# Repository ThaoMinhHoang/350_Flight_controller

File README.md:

# ECTE350 Flight controller
ECTE350 storage room for Locus team

Save the kicad files of your sensor. Put them into a folder. Name the folder after your sensor. Upload the folder to github.

The Development folder is all of our work in the one kicad file. Don't fuck with it unless you know what you're doing :)

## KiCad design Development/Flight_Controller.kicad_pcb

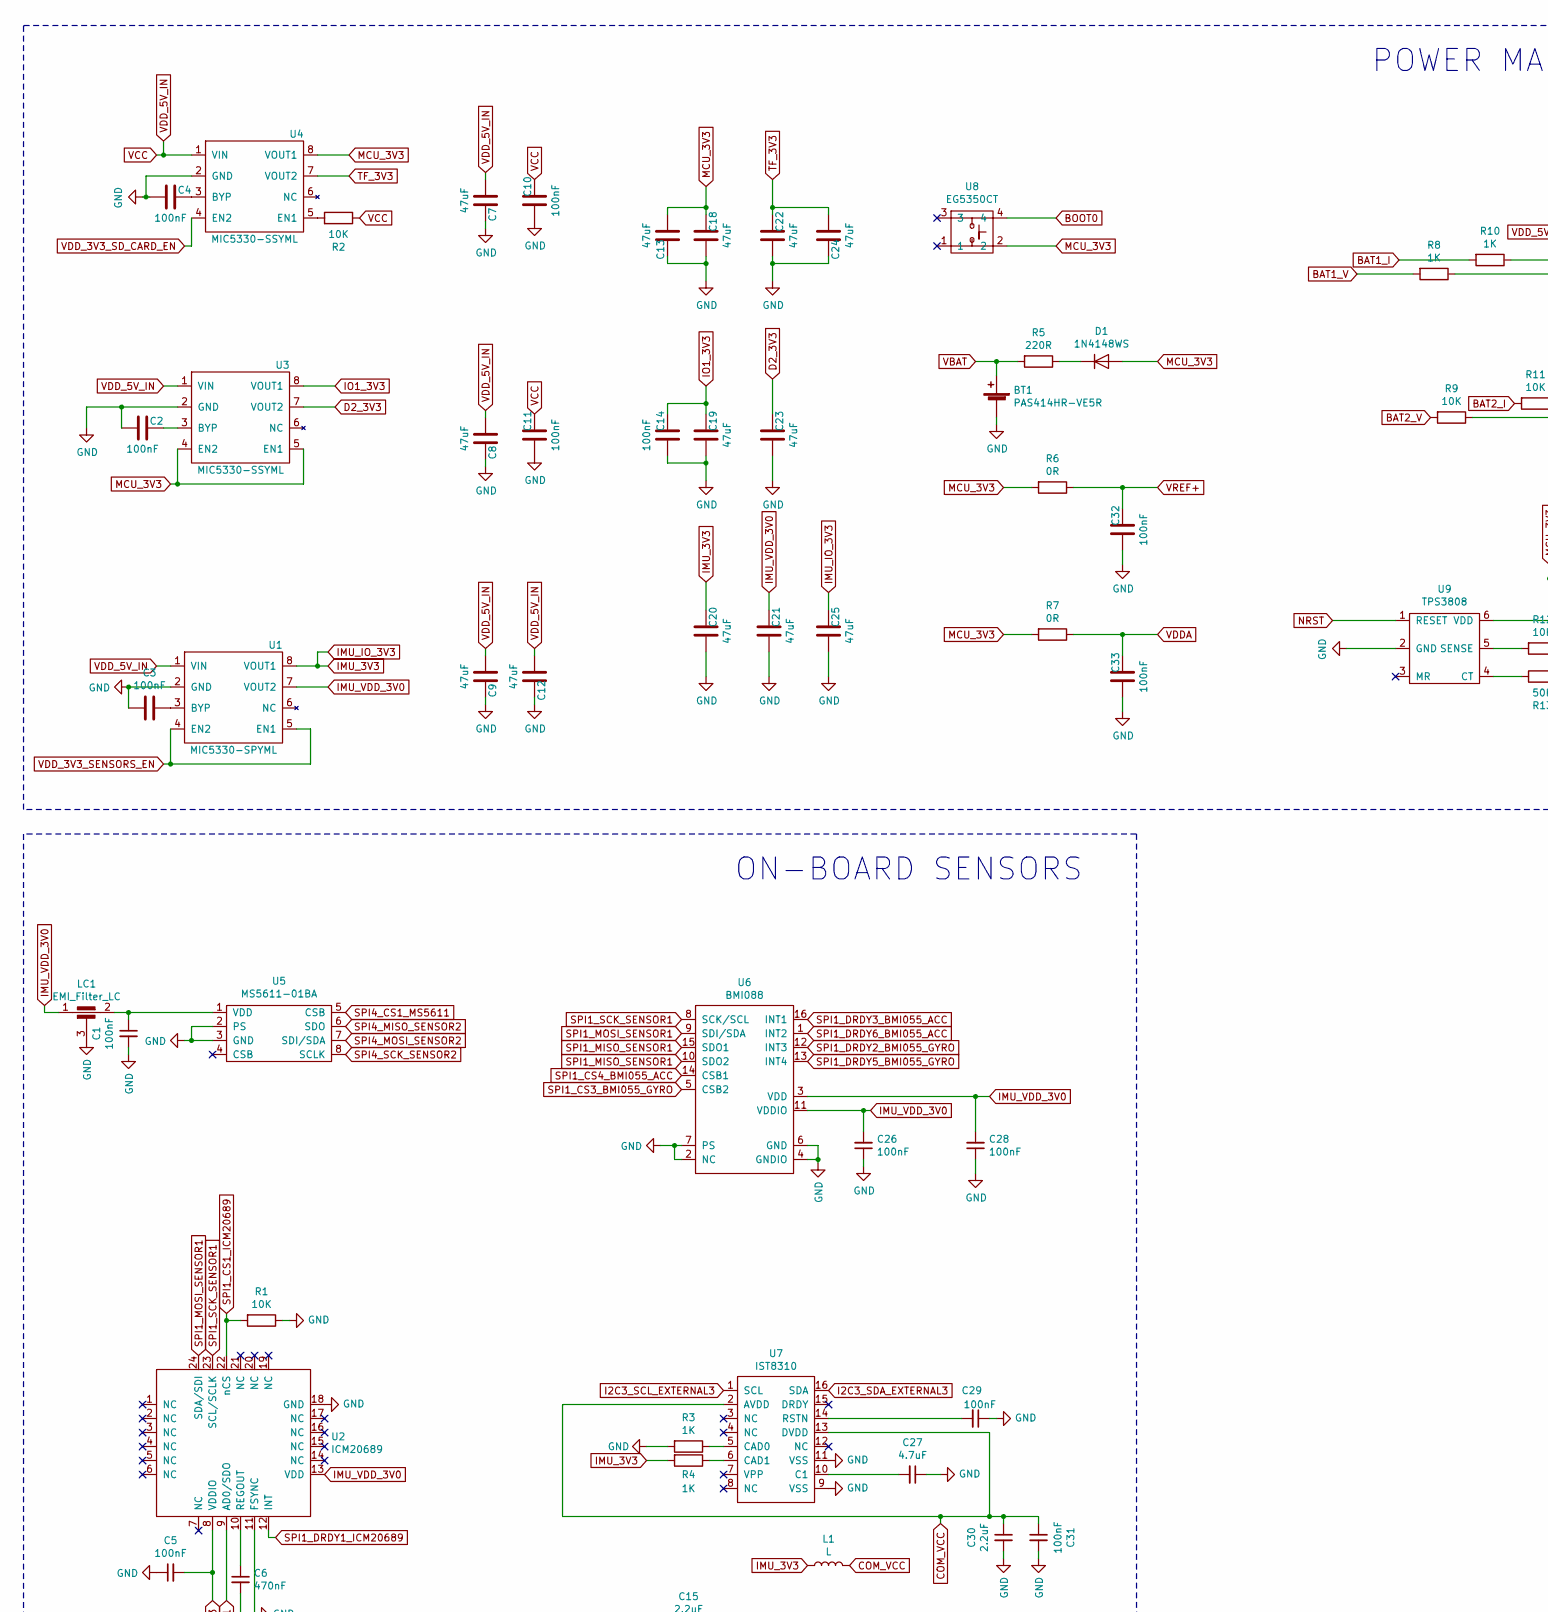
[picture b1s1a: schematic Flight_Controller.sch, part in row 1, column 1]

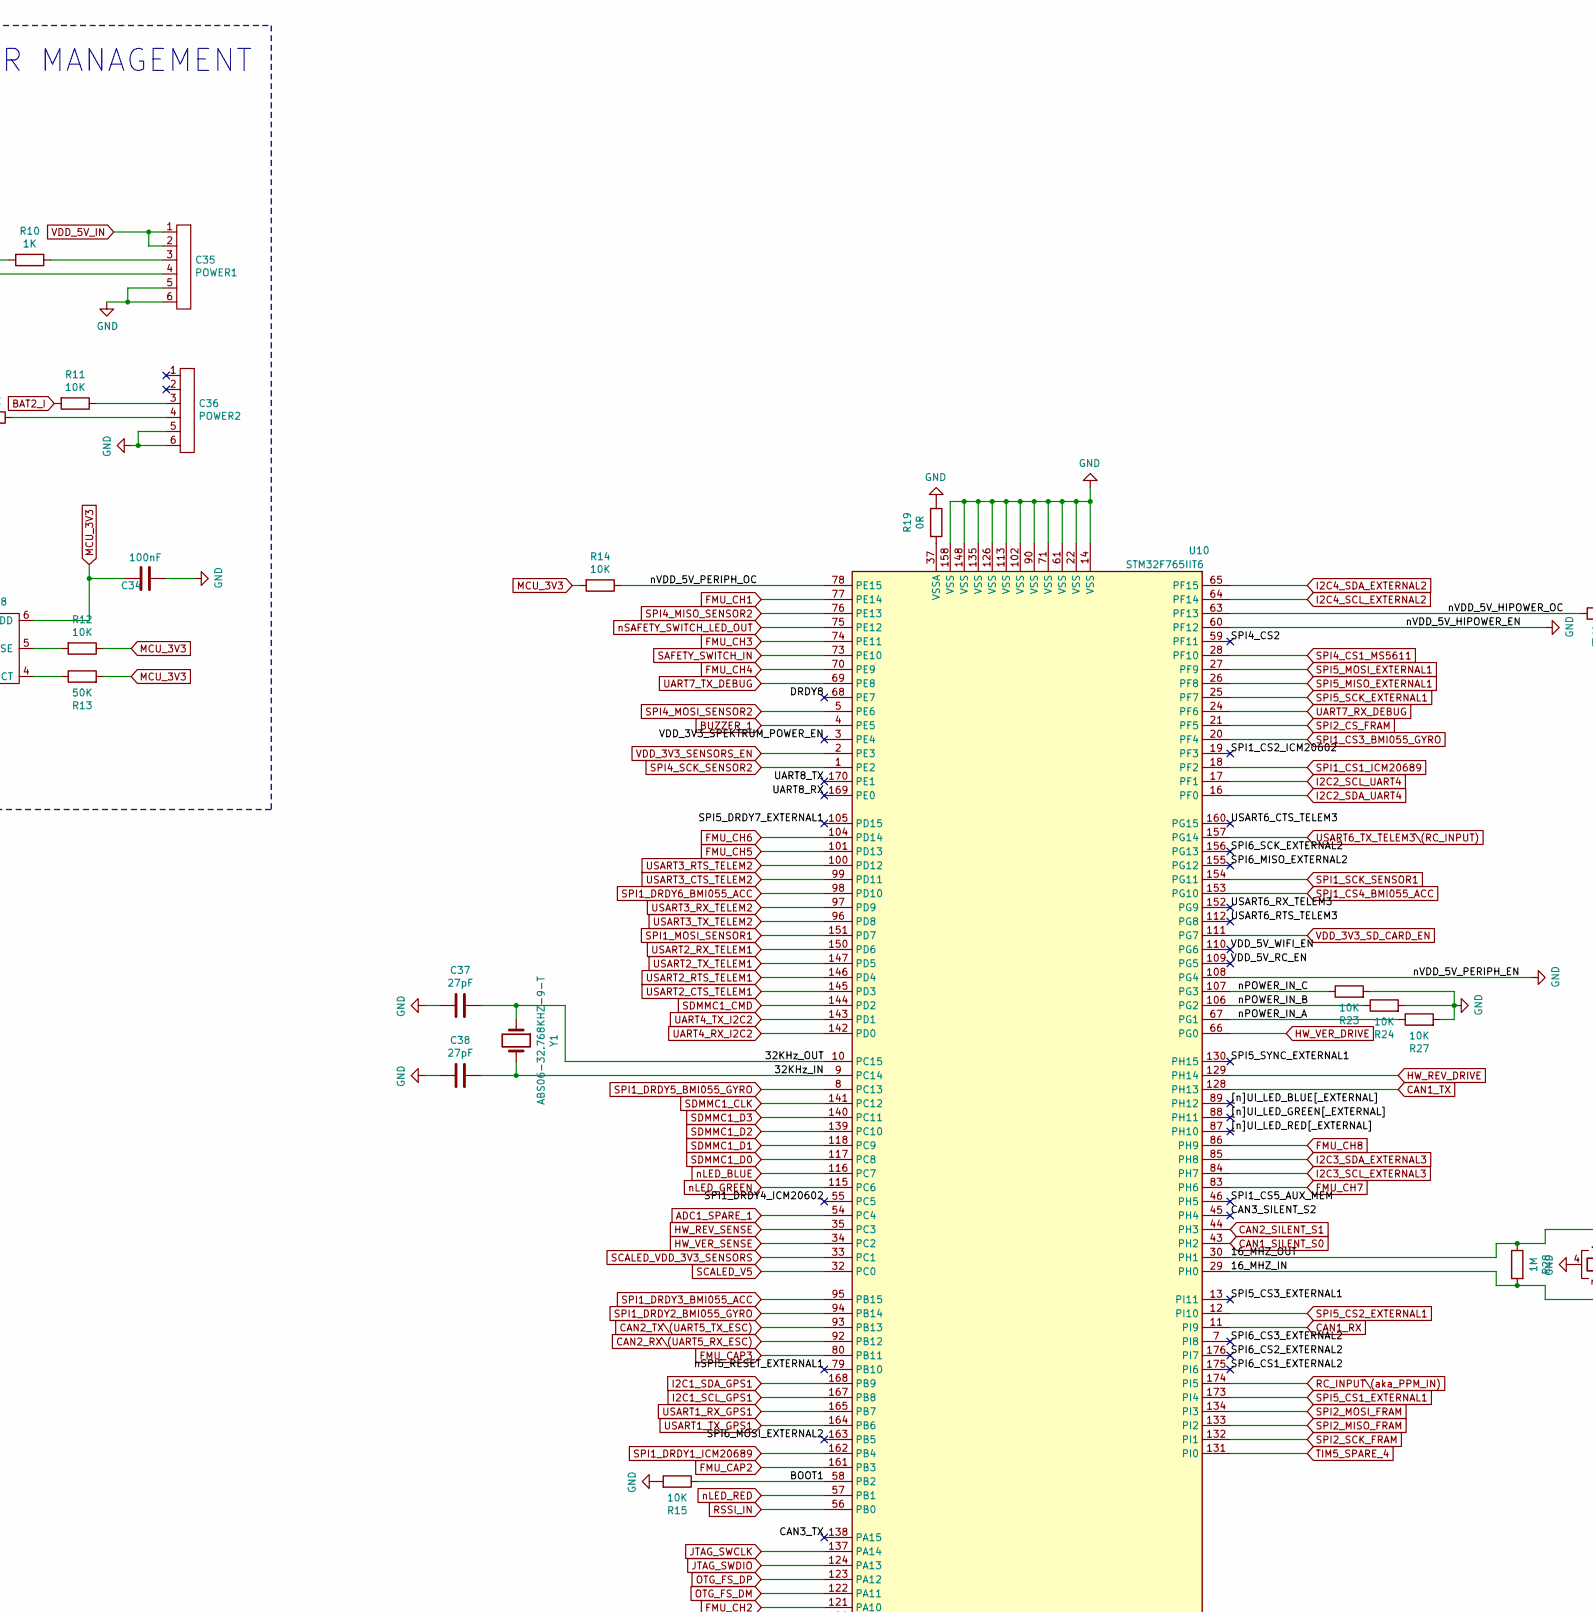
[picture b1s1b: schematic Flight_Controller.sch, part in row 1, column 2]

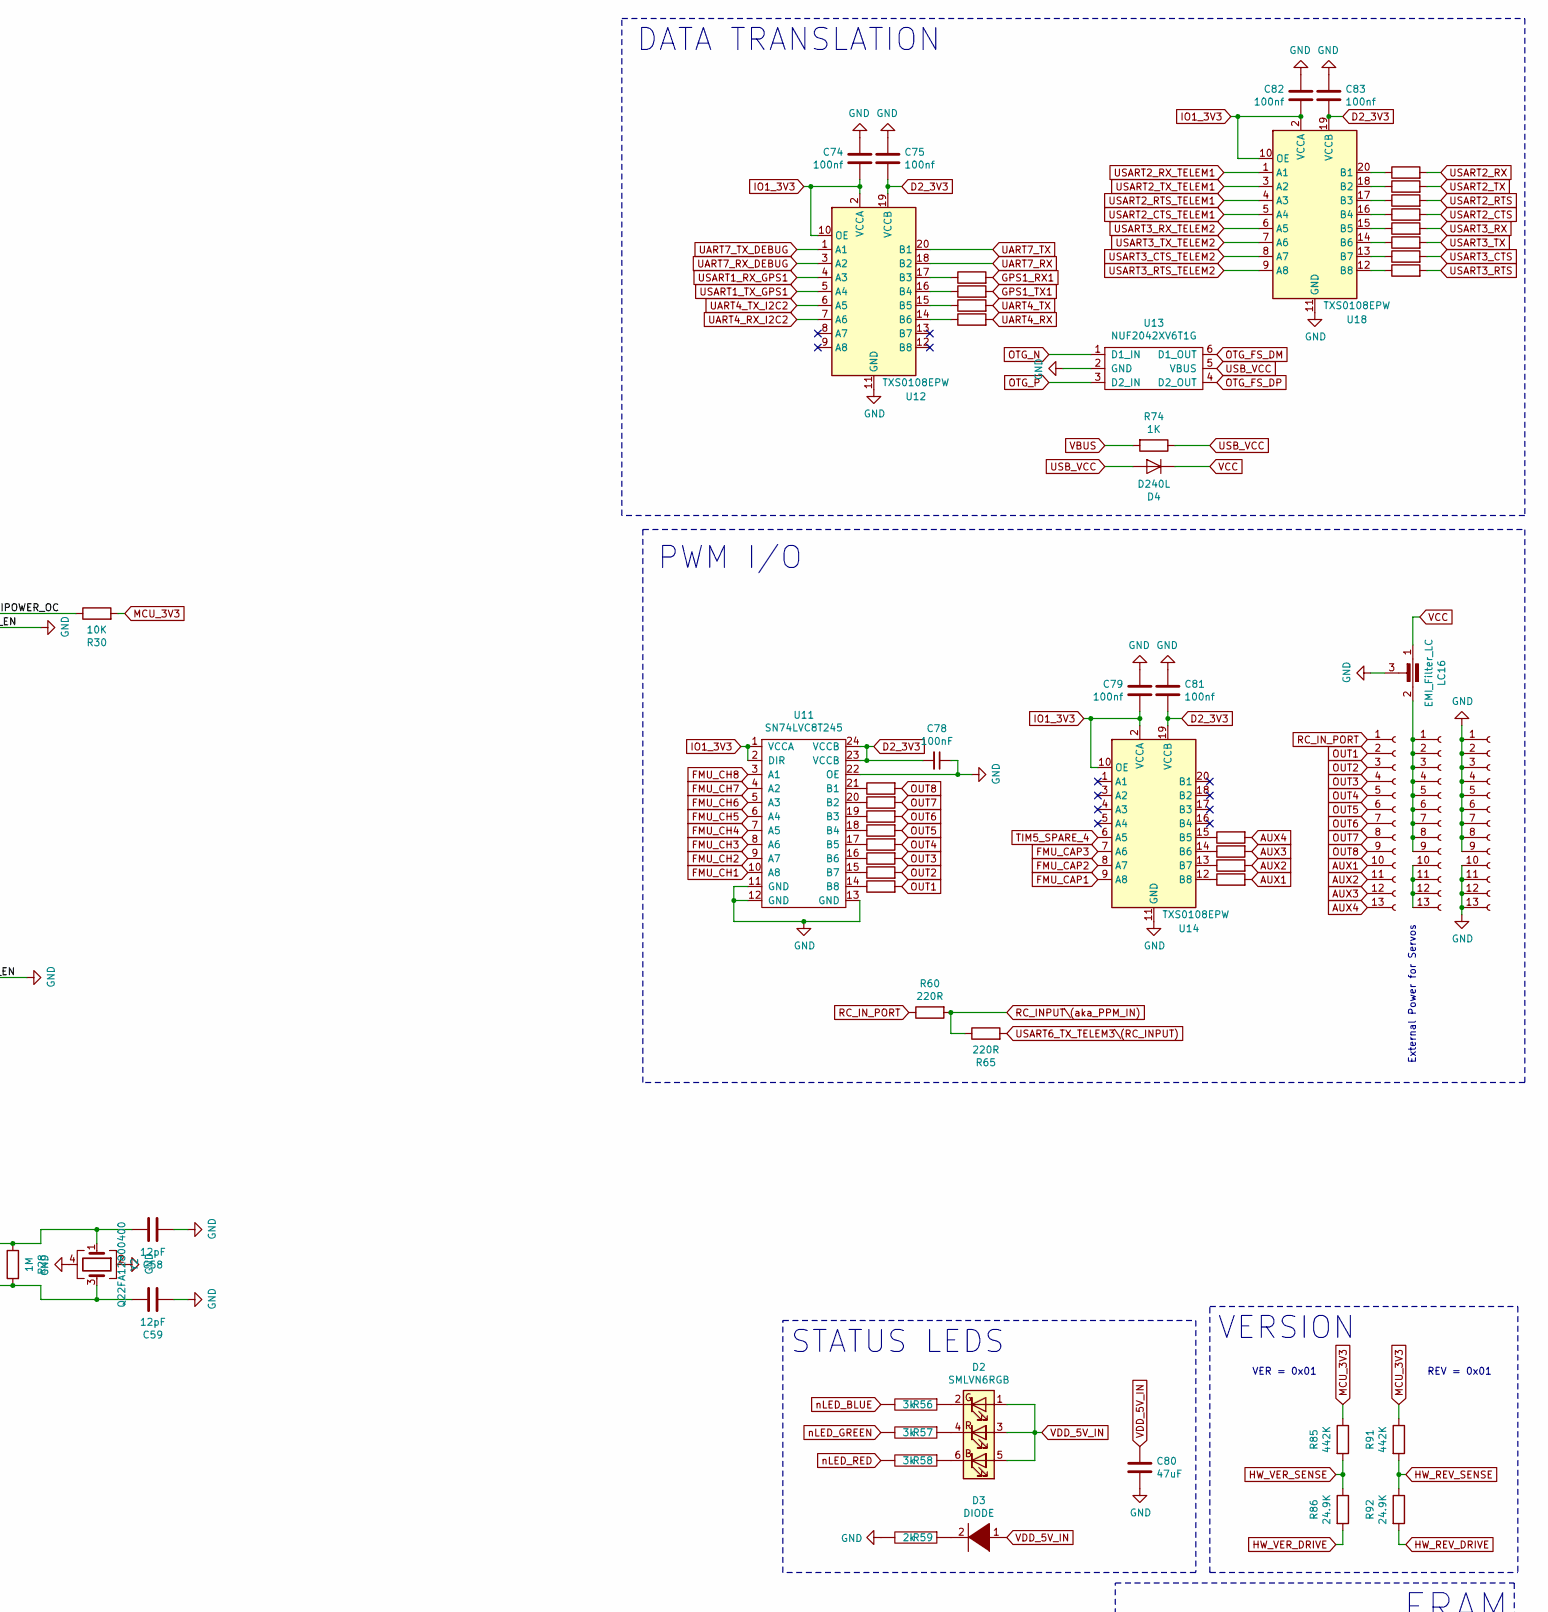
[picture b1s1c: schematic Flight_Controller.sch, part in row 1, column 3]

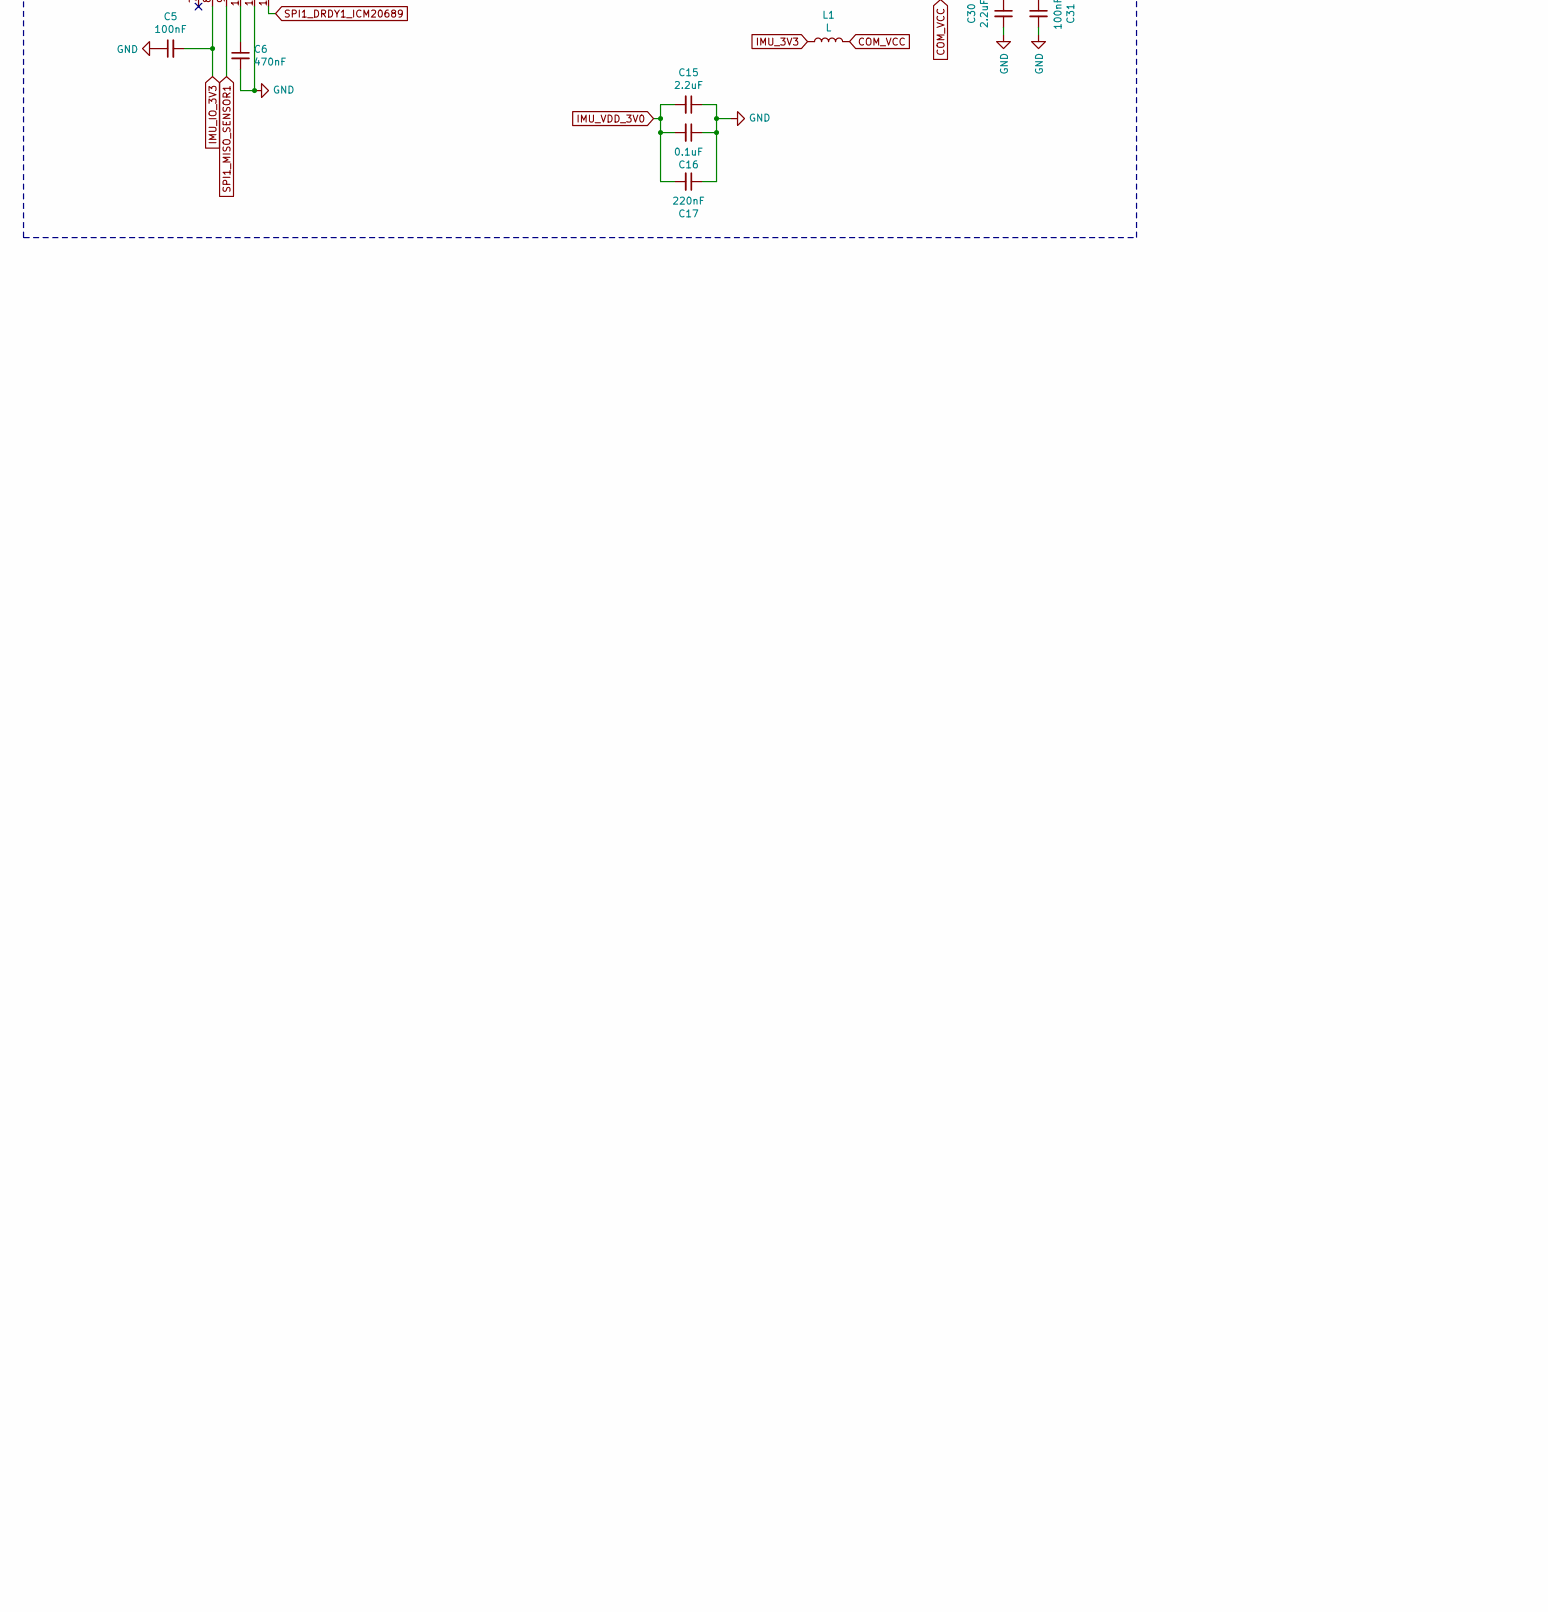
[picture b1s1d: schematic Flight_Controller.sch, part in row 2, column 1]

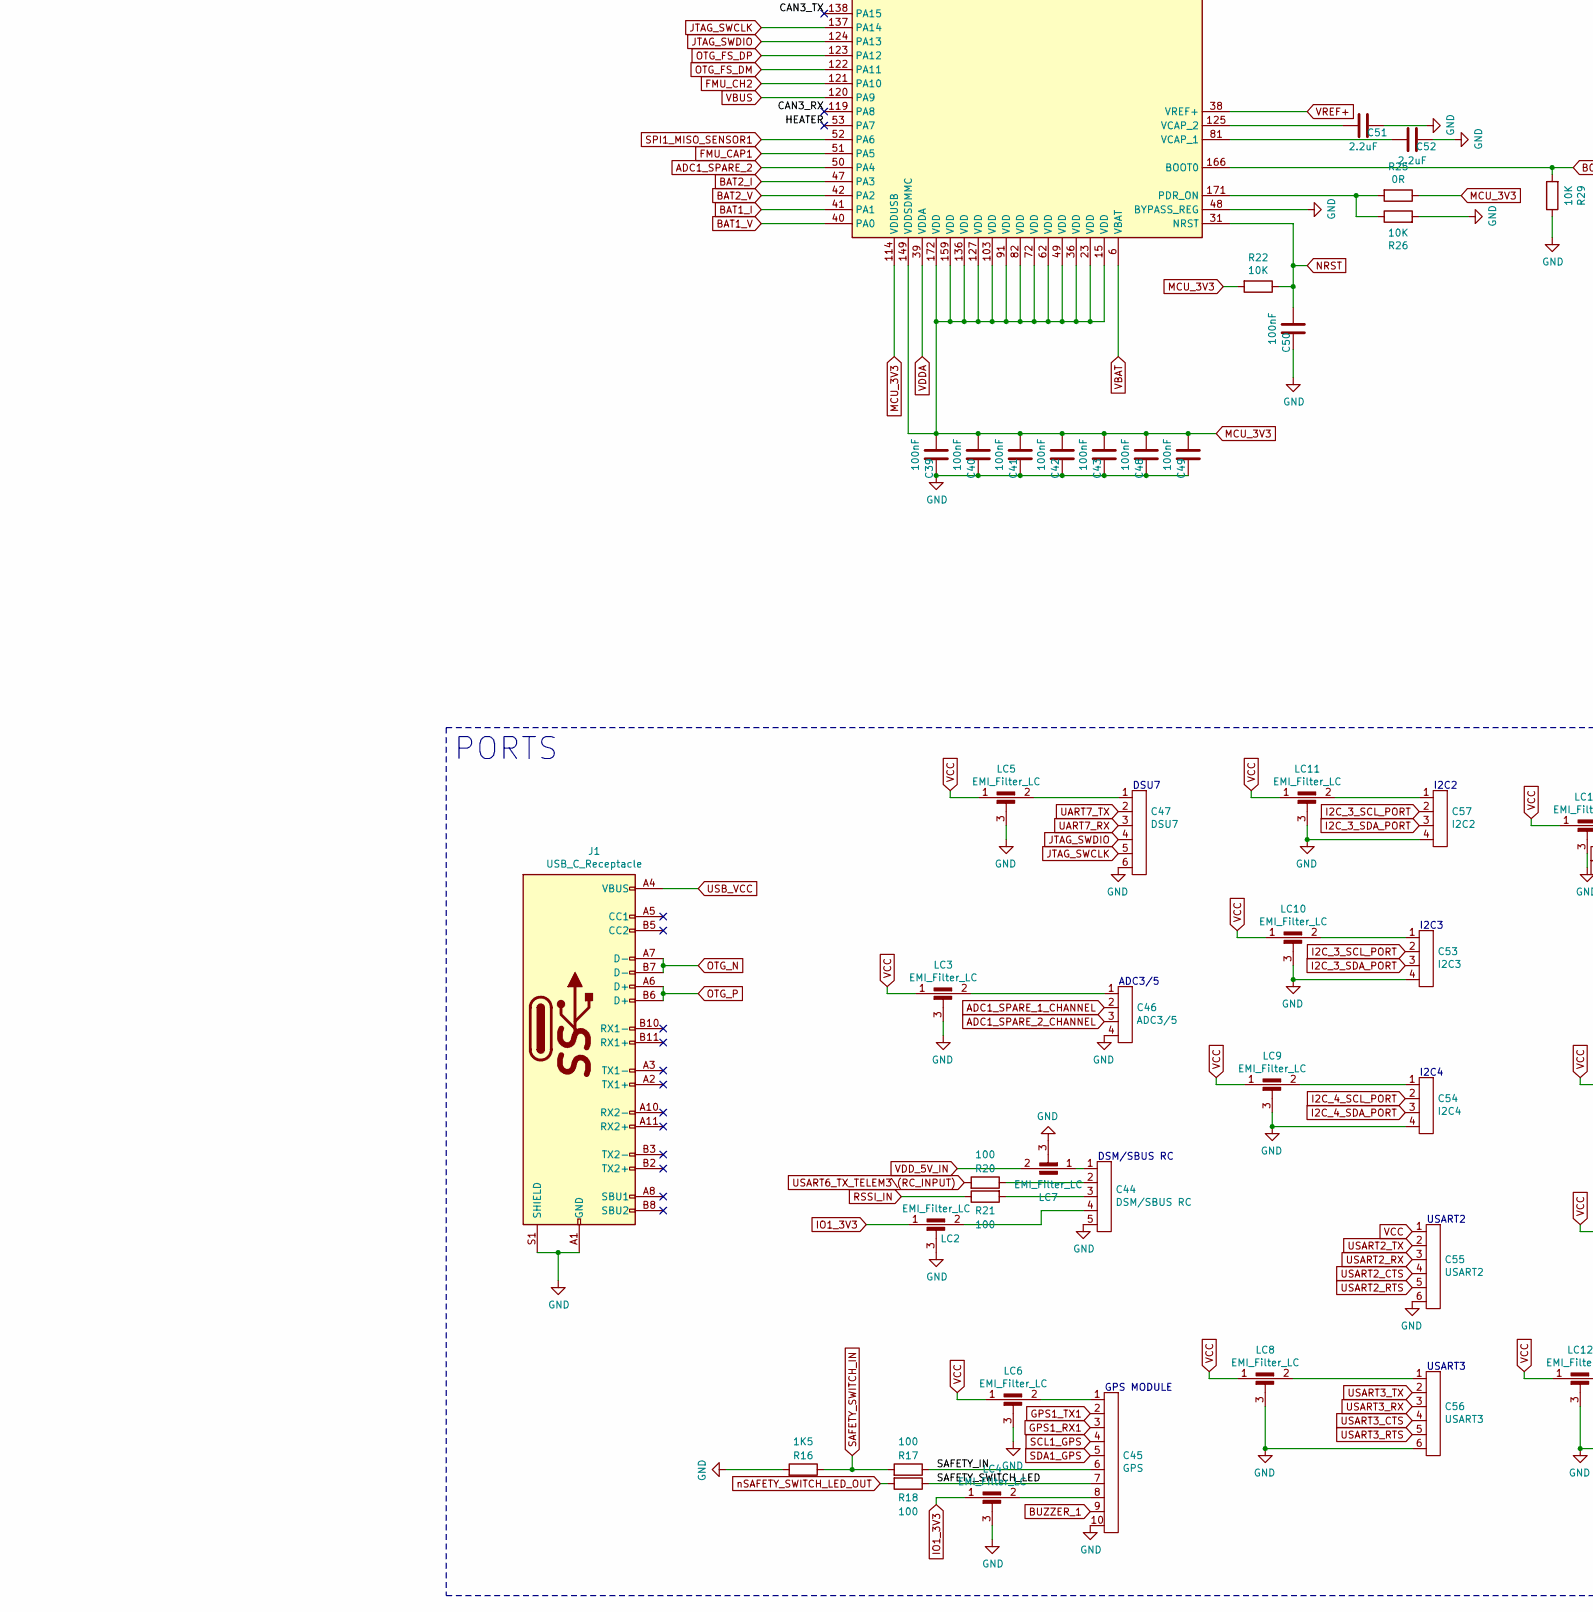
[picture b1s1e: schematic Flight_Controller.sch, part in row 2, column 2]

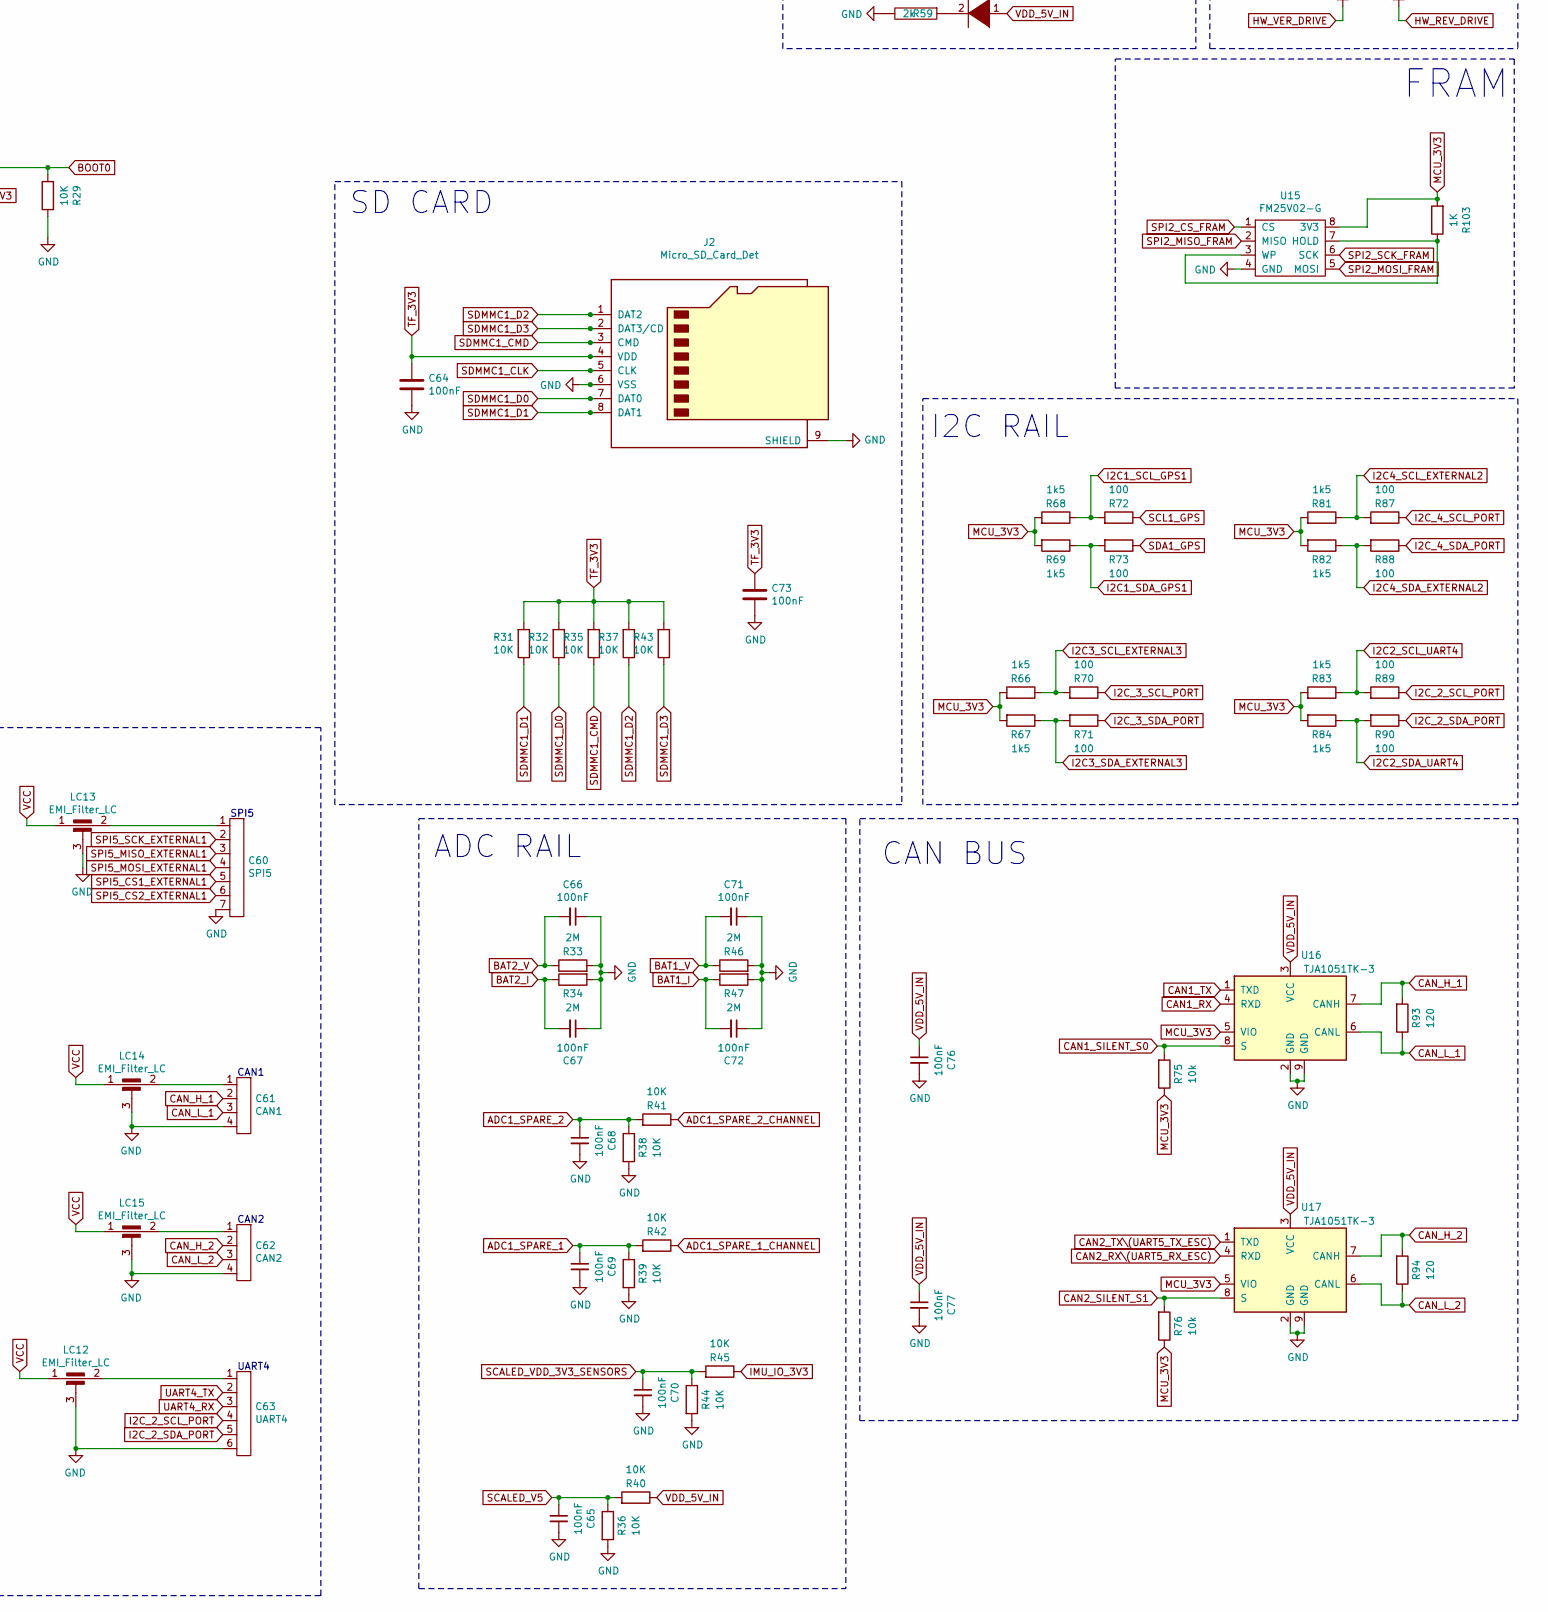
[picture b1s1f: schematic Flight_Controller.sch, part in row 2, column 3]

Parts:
BT1: PAS414HR-VE5R; UL_PAS414HRVE5R
C1, C2, C3, C4, C5, C10, C11, C14, C26, C28, C29, C31, C32, C33, C34, C39, C40, C41, C42, C43, C48, C49, C50, C64, C65, C66, C67, C68, C69, C70, C71, C72, C73, C76, C77, C78: 100nF; C_0402_1005Metric
C6: 470nF; C_0402_1005Metric
C7, C8, C9, C12, C13, C18, C19, C20, C21, C22, C23, C24, C25, C80: 47uF; C_0603_1608Metric
C15, C30, C51, C52: 2.2uF; C_0402_1005Metric
C16: 0.1uF; C_0402_1005Metric
C17: 220nF; C_0402_1005Metric
C27: 4.7uF; C_0402_1005Metric
C35: POWER1; JST_GH_BM06B-GHS-TBT_06x1.25mm_Straight
C36: POWER2; JST_GH_BM06B-GHS-TBT_06x1.25mm_Straight
C37, C38: 27pF; C_0402_1005Metric
C44: DSM/SBUS RC; JST_GH_BM05B-GHS-TBT_05x1.25mm_Straight
C45: GPS; JST_GH_BM10B-GHS-TBT_10x1.25mm_Straight
C46: ADC3/5; JST_GH_BM04B-GHS-TBT_04x1.25mm_Straight
C47: DSU7; JST_GH_BM06B-GHS-TBT_06x1.25mm_Straight
C53: I2C3; JST_GH_BM04B-GHS-TBT_04x1.25mm_Straight
C54: I2C4; JST_GH_BM04B-GHS-TBT_04x1.25mm_Straight
C55: USART2; JST_GH_BM06B-GHS-TBT_06x1.25mm_Straight
C56: USART3; JST_GH_BM06B-GHS-TBT_06x1.25mm_Straight
C57: I2C2; JST_GH_BM04B-GHS-TBT_04x1.25mm_Straight
C58, C59: 12pF; C_0402_1005Metric
C60: SPI5; JST_GH_BM07B-GHS-TBT_07x1.25mm_Straight
C61: CAN1; JST_GH_BM04B-GHS-TBT_04x1.25mm_Straight
C62: CAN2; JST_GH_BM04B-GHS-TBT_04x1.25mm_Straight
C63: UART4; JST_GH_BM06B-GHS-TBT_06x1.25mm_Straight
C74, C75, C79, C81, C82, C83: 100nf; C_0402_1005Metric
D1: 1N4148WS; D_SOD-323
D2: SMLVN6RGB; LED_ROHM_SMLVN6
D3: DIODE; LED_0603_1608Metric
D4: D240L; D_SOD-123
J1: USB_C_Receptacle; USB_C_Receptacle_Amphenol_12401610E4-2A_CircularHoles
J2: Micro_SD_Card_Det; microSD_HC_Hirose_DM3AT-SF-PEJM5
J3, J4, J5: Conn_01x13_Female; PinHeader_1x13_P2.54mm_Vertical
L1: L; L_0402_1005Metric
LC1, LC2, LC3, LC4, LC5, LC6, LC7, LC8, LC9, LC10, LC11, LC12, LC13, LC14, LC15, LC16: EMI_Filter_LC; FIL_NFM21PC105B1C3D
R1, R2, R9, R11, R12, R14, R15, R22, R23, R24, R26, R27, R29, R30, R31, R32, R35, R36, R37, R38, R39, R40, R41, R42, R43, R44, R45: 10K; R_0402_1005Metric
R3, R4, R8, R10, R74, R103: 1K; R_0402_1005Metric
R5, R60, R65: 220R; R_0402_1005Metric
R6, R7, R19, R25: 0R; R_0402_1005Metric
R13: 50K; R_0402_1005Metric
R16: 1K5; R_0402_1005Metric
R17, R18, R20, R21, R48, R49, R50, R51, R52, R53, R54, R55, R70, R71, R72, R73, R77, R78, R79, R80, R87, R88, R89, R90: 100; R_0402_1005Metric
R28: 1M; R_0402_1005Metric
R33, R34, R46, R47: 2M; R_0402_1005Metric
R56, R57, R58: 3k; R_0402_1005Metric
R59: 2k; R_0402_1005Metric
R61, R62, R63, R64, R95, R96, R97, R98, R99, R100, R101, R102: 100R; R_0402_1005Metric
R66, R67, R68, R69, R81, R82, R83, R84: 1k5; R_0402_1005Metric
R75, R76: 10k; R_0402_1005Metric
R85, R91: 442K; R_0402_1005Metric
R86, R92: 24.9K; R_0402_1005Metric
R93, R94: 120; R_0402_1005Metric
U1: MIC5330-SPYML; MIC5330-SSYML-TR
U2: ICM20689
U3, U4: MIC5330-SSYML; MIC5330-SSYML-TR
U5: MS5611-01BA; ms5611
U6: BMI088
U7: IST8310; ist8310
U8: EG5350CT; SW_SPST_EVQP7C
U9: TPS3808; SOT95P280X145-6N
U10: STM32F765IIT6; LQFP-176_24x24mm_P0.5mm
U11: SN74LVC8T245; SOP65P640X120-24N
U12, U14, U18: TXS0108EPW; TSSOP-20_4.4x6.5mm_P0.65mm
U13: NUF2042XV6T1G; SOT50P160X60-6N
U15: FM25V02-G
U16, U17: TJA1051TK-3; DFN-8-1EP_3x3mm_P0.65mm_EP1.55x2.4mm
Y1: ABS06-32.768KHZ-9-T; XTAL_ABS06-32.768KHZ-9-T
Y2: Q22FA12800400

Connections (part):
/16_MHZ_IN: C59.1, R28.2, U10.29 (PH0), Y2.3
/16_MHZ_OUT: C58.1, R28.1, U10.30 (PH1), Y2.1
/32KHz_IN: C38.1, U10.9 (PC14), Y1.2
/32KHz_OUT: C37.1, U10.10 (PC15), Y1.1
/BOOT1: R15.1, U10.58 (PB2)
/CAN3_RX: U10.119 (PA8)
/CAN3_SILENT_S2: U10.45 (PH4)
/CAN3_TX: U10.138 (PA15)
/DRDY8: U10.68 (PE7)
/HEATER: U10.53 (PA7)
/SAFETY_IN: C45.6, R17.1
/SAFETY_SWITCH_LED: C45.7, R18.1
/SPI1_CS2_ICM20602: U10.19 (PF3)
/SPI1_CS5_AUX_MEM: U10.46 (PH5)
/SPI1_DRDY4_ICM20602: U10.55 (PC5)
/SPI4_CS2: U10.59 (PF11)
/SPI5_CS3_EXTERNAL1: U10.13 (PI11)
/SPI5_DRDY7_EXTERNAL1: U10.105 (PD15)
/SPI5_SYNC_EXTERNAL1: U10.130 (PH15)
/SPI6_CS1_EXTERNAL2: U10.175 (PI6)
/SPI6_CS2_EXTERNAL2: U10.176 (PI7)
/SPI6_CS3_EXTERNAL2: U10.7 (PI8)
/SPI6_MISO_EXTERNAL2: U10.155 (PG12)
/SPI6_MOSI_EXTERNAL2: U10.163 (PB5)
/SPI6_SCK_EXTERNAL2: U10.156 (PG13)
/UART8_RX: U10.169 (PE0)
/UART8_TX: U10.170 (PE1)
/USART6_CTS_TELEM3: U10.160 (PG15)
/USART6_RTS_TELEM3: U10.112 (PG8)
/USART6_RX_TELEM3: U10.152 (PG9)
/VDD_3V3_SPEKTRUM_POWER_EN: U10.3 (PE4)
/VDD_5V_RC_EN: U10.109 (PG5)
/VDD_5V_WIFI_EN: U10.110 (PG6)
/[n]UI_LED_BLUE[_EXTERNAL]: U10.89 (PH12)
/[n]UI_LED_GREEN[_EXTERNAL]: U10.88 (PH11)
/[n]UI_LED_RED[_EXTERNAL]: U10.87 (PH10)
/nPOWER_IN_A: R27.1, U10.67 (PG1)
/nPOWER_IN_B: R24.1, U10.106 (PG2)
/nPOWER_IN_C: R23.1, U10.107 (PG3)
/nSPI5_RESET_EXTERNAL1: U10.79 (PB10)
/nVDD_5V_HIPOWER_OC: R30.1, U10.63 (PF13)
/nVDD_5V_PERIPH_OC: R14.1, U10.78 (PE15)
ADC1_SPARE_1: C69.1, R39.1, R42.2, U10.54 (PC4)
ADC1_SPARE_1_CHANNEL: C46.2, R42.1
ADC1_SPARE_2: C68.1, R38.1, R41.2, U10.50 (PA4)
ADC1_SPARE_2_CHANNEL: C46.3, R41.1
AUX1: J3.10, R80.2
AUX2: J3.11, R79.2
AUX3: J3.12, R78.2
AUX4: J3.13, R77.2
BAT1_I: C72.2, R10.2, R47.1, U10.41 (PA1)
BAT1_V: C71.2, R8.2, R46.1, U10.40 (PA0)
BAT2_I: C67.2, R11.2, R34.1, U10.47 (PA3)
BAT2_V: C66.2, R9.2, R33.1, U10.42 (PA2)
BOOT0: R29.2, U8.4, U10.166 (BOOT0)
BUZZER_1: C45.9, U10.4 (PE5)
CAN1_RX: U10.11 (PI9), U16.4 (RXD)
CAN1_SILENT_S0: R75.2, U10.43 (PH2), U16.8 (S)
CAN1_TX: U10.128 (PH13), U16.1 (TXD)
CAN2_RX\(UART5_RX_ESC): U10.92 (PB12), U17.4 (RXD)
CAN2_SILENT_S1: R76.2, U10.44 (PH3), U17.8 (S)
CAN2_TX\(UART5_TX_ESC): U10.93 (PB13), U17.1 (TXD)
CAN_H_1: C61.2, R93.2, U16.7 (CANH)
CAN_H_2: C62.2, R94.2, U17.7 (CANH)
CAN_L_1: C61.3, R93.1, U16.6 (CANL)
CAN_L_2: C62.3, R94.1, U17.6 (CANL)
COM_VCC: C30.1, C31.1, L1.2, U7.2 (AVDD), U7.13 (DVDD)
D2_3V3: C23.2, C75.2, C78.2, C81.2, C83.2, U3.7 (VOUT2), U11.23 (VCCB), U11.24 (VCCB), U12.19 (VCCB), U14.19 (VCCB), U18.19 (VCCB)
FMU_CAP1: U10.51 (PA5), U14.9 (A8)
FMU_CAP2: U10.161 (PB3), U14.8 (A7)
FMU_CAP3: U10.80 (PB11), U14.7 (A6)
FMU_CH1: U10.77 (PE14), U11.10 (A8)
FMU_CH2: U10.121 (PA10), U11.9 (A7)
FMU_CH3: U10.74 (PE11), U11.8 (A6)
FMU_CH4: U10.70 (PE9), U11.7 (A5)
FMU_CH5: U10.101 (PD13), U11.6 (A4)
FMU_CH6: U10.104 (PD14), U11.5 (A3)
FMU_CH7: U10.83 (PH6), U11.4 (A2)
FMU_CH8: U10.86 (PH9), U11.3 (A1)
GND: BT1.2 (-), C1.2, C2.2, C3.1, C4.2, C5.1, C6.2, C7.1, C8.1, C9.1, C10.2, C11.2, C12.1, C13.2, C14.1, C15.1, C16.1, C17.1, C18.1, C19.1, C20.1, C21.1, C22.1, C23.1, C24.2, C25.1, C26.1, C27.1, C28.1, C29.1, C30.2, C31.2, C32.2, C33.2, C34.2, C35.5, C35.6, C36.5, C36.6, C37.2, C38.2, C39.2, C40.2, C41.2, C42.2, C43.2, C44.5, C45.10, C46.4, C47.6, C48.2, C49.2, C50.2, C51.2, C52.2, C53.4, C54.4, C55.6, C56.6, C57.4, C58.2, C59.2, C60.7, C61.4, C62.4, C63.6, C64.2, C65.2, C66.1, C67.1, C68.2, C69.2, C70.2, C71.1, C72.1, C73.2, C74.1, C75.1, C76.2, C77.2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
GPS1_RX1: C45.3, R61.2
GPS1_TX1: C45.2, R62.2
HW_REV_DRIVE: R92.2, U10.129 (PH14)
HW_REV_SENSE: R91.2, R92.1, U10.35 (PC3)
HW_VER_DRIVE: R86.2, U10.66 (PG0)
HW_VER_SENSE: R85.2, R86.1, U10.34 (PC2)
I2C1_SCL_GPS1: R68.1, R72.2, U10.167 (PB8)
I2C1_SDA_GPS1: R69.1, R73.2, U10.168 (PB9)
I2C2_SCL_UART4: R83.1, R89.2, U10.17 (PF1)
I2C2_SDA_UART4: R84.1, R90.2, U10.16 (PF0)
I2C3_SCL_EXTERNAL3: R66.1, R70.2, U7.1 (SCL), U10.84 (PH7)
I2C3_SDA_EXTERNAL3: R67.1, R71.2, U7.16 (SDA), U10.85 (PH8)
I2C4_SCL_EXTERNAL2: R81.1, R87.2, U10.64 (PF14)
I2C4_SDA_EXTERNAL2: R82.1, R88.2, U10.65 (PF15)
I2C_2_SCL_PORT: C63.4, R89.1
I2C_2_SDA_PORT: C63.5, R90.1
I2C_3_SCL_PORT: C53.2, C57.2, R70.1
I2C_3_SDA_PORT: C53.3, C57.3, R71.1
I2C_4_SCL_PORT: C54.2, R87.1
I2C_4_SDA_PORT: C54.3, R88.1
IMU_3V3: C5.2, C20.2, C25.2, L1.1, R4.2, R45.1, U1.8 (VOUT1), U2.8 (VDDIO)
IMU_VDD_3V0: C15.2, C16.2, C17.2, C21.2, C26.2, C28.2, LC1.1, U1.7 (VOUT2), U2.13 (VDD), U6.3 (VDD), U6.11 (VDDIO)
IO1_3V3: C14.2, C19.2, C74.2, C79.2, C82.2, LC2.1, LC4.1, U3.8 (VOUT1), U11.1 (VCCA), U11.2 (DIR), U12.2 (VCCA), U12.10 (OE), U14.2 (VCCA), U14.10 (OE), U18.2 (VCCA), U18.10 (OE)
JTAG_SWCLK: C47.5, U10.137 (PA14)
JTAG_SWDIO: C47.4, U10.124 (PA13)
MCU_3V3: C13.1, C18.2, C34.1, C39.1, C40.1, C41.1, C42.1, C43.1, C48.1, C49.1, D1.2 (A), R6.2, R7.2, R12.1, R13.2, R14.2, R22.2, R25.1, R30.2, R66.2, R67.2, R68.2, R69.2, R75.1, R76.1, R81.2, R82.2, R83.2, R84.2, R85.1, R91.1, R103.2, U3.4 (EN2), U3.5 (EN1), U4.8 (VOUT1), U8.2, U9.6 (VDD), U10.15 (VDD), U10.23 (VDD), U10.36 (VDD), U10.49 (VDD), U10.62 (VDD), U10.72 (VDD), U10.82 (VDD), U10.91 (VDD), U10.103 (VDD), U10.114 (VDDUSB), U10.127 (VDD), U10.136 (VDD), U10.149 (VDDSDMMC), U10.159 (VDD), U10.172 (VDD), U15.8 (3V3), U16.5 (VIO), U17.5 (VIO)
NRST: C50.1, R22.1, U9.1 (RESET), U10.31 (NRST)
unnamed: C1.1, LC1.2, U5.1 (VDD)
unnamed: C2.1, U3.3 (BYP)
unnamed: C3.2, U1.3 (BYP)
unnamed: C4.1, U4.3 (BYP)
unnamed: C6.1, U2.10 (REGOUT)
unnamed: C27.2, U7.10 (C1)
unnamed: C29.2, U7.14 (RSTN)
unnamed: C35.3, R10.1
unnamed: C35.4, R8.1
unnamed: C36.3, R11.1
unnamed: C36.4, R9.1
unnamed: C44.1, LC7.1
unnamed: C44.2, R20.1
unnamed: C44.3, R21.2
unnamed: C44.4, LC2.2
unnamed: C45.1, LC6.2
unnamed: C45.8, LC4.2
unnamed: C46.1, LC3.2
unnamed: C47.1, LC5.2
unnamed: C51.1, U10.125 (VCAP_2)
unnamed: C52.1, U10.81 (VCAP_1)
unnamed: C53.1, LC10.2
unnamed: C54.1, LC9.2
unnamed: C56.1, LC8.2
unnamed: C57.1, LC11.2
unnamed: C60.1, LC13.2
unnamed: C61.1, LC14.2
unnamed: C62.1, LC15.2
unnamed: C63.1, LC12.2
unnamed: D1.1 (K), R5.1
unnamed: D2.2 (GK), R56.1
unnamed: D2.4 (RK), R57.1
unnamed: D2.6 (BK), R58.1
unnamed: D3.2 (A), R59.1
unnamed: J4.1, J4.2, J4.3, J4.4, J4.5, J4.6, J4.7, J4.8, J4.9, LC16.2
unnamed: J4.10, J4.11, J4.12, J4.13
unnamed: R2.2, U4.5 (EN1)
unnamed: R3.1, U7.5 (CAD0)
unnamed: R4.1, U7.6 (CAD1)
unnamed: R12.2, U9.5 (SENSE)
unnamed: R13.1, U9.4 (CT)
unnamed: R19.2, U10.37 (VSSA)
unnamed: R25.2, R26.1, U10.171 (PDR_ON)
unnamed: R48.1, U11.21 (B1)
unnamed: R49.1, U11.20 (B2)
unnamed: R50.1, U11.19 (B3)
unnamed: R51.1, U11.18 (B4)
unnamed: R52.1, U11.17 (B5)
unnamed: R53.1, U11.16 (B6)
unnamed: R54.1, U11.15 (B7)
unnamed: R55.1, U11.14 (B8)
unnamed: R61.1, U12.17 (B3)
unnamed: R62.1, U12.16 (B4)
unnamed: R63.1, U12.15 (B5)
unnamed: R64.1, U12.14 (B6)
unnamed: R77.1, U14.15 (B5)
unnamed: R78.1, U14.14 (B6)
unnamed: R79.1, U14.13 (B7)
unnamed: R80.1, U14.12 (B8)
unnamed: R95.1, U18.20 (B1)
unnamed: R96.1, U18.18 (B2)
unnamed: R97.1, U18.17 (B3)
unnamed: R98.1, U18.16 (B4)
unnamed: R99.1, U18.15 (B5)
unnamed: R100.1, U18.14 (B6)
unnamed: R101.1, U18.13 (B7)
unnamed: R102.1, U18.12 (B8)
unnamed: R103.1, U15.3 (WP), U15.7 (HOLD)
OTG_FS_DM: U10.122 (PA11), U13.6 (D1_OUT)
OTG_FS_DP: U10.123 (PA12), U13.4 (D2_OUT)
OTG_N: J1.A7 (D-), J1.B7 (D-), U13.1 (D1_IN)
OTG_P: J1.A6 (D+), J1.B6 (D+), U13.3 (D2_IN)
OUT1: J3.2, R55.2
OUT2: J3.3, R54.2
OUT3: J3.4, R53.2
OUT4: J3.5, R52.2
OUT5: J3.6, R51.2
OUT6: J3.7, R50.2
OUT7: J3.8, R49.2
OUT8: J3.9, R48.2
RC_INPUT\(aka_PPM_IN): R60.2, R65.1, U10.174 (PI5)
RC_IN_PORT: J3.1, R60.1
RSSI_IN: R21.1, U10.56 (PB0)
SAFETY_SWITCH_IN: R16.1, R17.2, U10.73 (PE10)
SCALED_V5: C65.1, R36.1, R40.2, U10.32 (PC0)
SCALED_VDD_3V3_SENSORS: C70.1, R44.1, R45.2, U10.33 (PC1)
SCL1_GPS: C45.4, R72.1
SDA1_GPS: C45.5, R73.1
SDMMC1_CLK: J2.5 (CLK), U10.141 (PC12)
SDMMC1_CMD: J2.3 (CMD), R35.1, U10.144 (PD2)
SDMMC1_D0: J2.7 (DAT0), R32.1, U10.117 (PC8)
SDMMC1_D1: J2.8 (DAT1), R31.1, U10.118 (PC9)
SDMMC1_D2: J2.1 (DAT2), R37.1, U10.139 (PC10)
SDMMC1_D3: J2.2 (DAT3/CD), R43.1, U10.140 (PC11)
SPI1_CS1_ICM20689: R1.2, U2.22 (nCS), U10.18 (PF2)
SPI1_CS3_BMI055_GYRO: U6.5 (CSB2), U10.20 (PF4)
SPI1_CS4_BMI055_ACC: U6.14 (CSB1), U10.153 (PG10)
SPI1_DRDY1_ICM20689: U2.12 (INT), U10.162 (PB4)
SPI1_DRDY2_BMI055_GYRO: U6.12 (INT3), U10.94 (PB14)
SPI1_DRDY3_BMI055_ACC: U6.16 (INT1), U10.95 (PB15)
SPI1_DRDY5_BMI055_GYRO: U6.13 (INT4), U10.8 (PC13)
SPI1_DRDY6_BMI055_ACC: U6.1 (INT2), U10.98 (PD10)
SPI1_MISO_SENSOR1: U2.9 (AD0/SDO), U6.10 (SDO2), U6.15 (SDO1), U10.52 (PA6)
SPI1_MOSI_SENSOR1: U2.24 (SDA/SDI), U6.9 (SDI/SDA), U10.151 (PD7)
SPI1_SCK_SENSOR1: U2.23 (SCL/SCLK), U6.8 (SCK/SCL), U10.154 (PG11)
SPI2_CS_FRAM: U10.21 (PF5), U15.1 (CS)
SPI2_MISO_FRAM: U10.133 (PI2), U15.2 (MISO)
SPI2_MOSI_FRAM: U10.134 (PI3), U15.5 (MOSI)
SPI2_SCK_FRAM: U10.132 (PI1), U15.6 (SCK)
SPI4_CS1_MS5611: U5.5 (CSB), U10.28 (PF10)
SPI4_MISO_SENSOR2: U5.6 (SDO), U10.76 (PE13)
SPI4_MOSI_SENSOR2: U5.7 (SDI/SDA), U10.5 (PE6)
SPI4_SCK_SENSOR2: U5.8 (SCLK), U10.1 (PE2)
SPI5_CS1_EXTERNAL1: C60.5, U10.173 (PI4)
SPI5_CS2_EXTERNAL1: C60.6, U10.12 (PI10)
SPI5_MISO_EXTERNAL1: C60.3, U10.26 (PF8)
SPI5_MOSI_EXTERNAL1: C60.4, U10.27 (PF9)
SPI5_SCK_EXTERNAL1: C60.2, U10.25 (PF7)
TF_3V3: C22.2, C24.1, C64.1, C73.1, J2.4 (VDD), R31.2, R32.2, R35.2, R37.2, R43.2, U4.7 (VOUT2)
TIM5_SPARE_4: U10.131 (PI0), U14.6 (A5)
UART4_RX: C63.3, R64.2
UART4_RX_I2C2: U10.142 (PD0), U12.7 (A6)
UART4_TX: C63.2, R63.2
UART4_TX_I2C2: U10.143 (PD1), U12.6 (A5)
UART7_RX: C47.3, U12.18 (B2)
UART7_RX_DEBUG: U10.24 (PF6), U12.3 (A2)
UART7_TX: C47.2, U12.20 (B1)
UART7_TX_DEBUG: U10.69 (PE8), U12.1 (A1)
USART1_RX_GPS1: U10.165 (PB7), U12.4 (A3)
USART1_TX_GPS1: U10.164 (PB6), U12.5 (A4)
USART2_CTS: C55.4, R98.2
USART2_CTS_TELEM1: U10.145 (PD3), U18.5 (A4)
USART2_RTS: C55.5, R97.2
USART2_RTS_TELEM1: U10.146 (PD4), U18.4 (A3)
USART2_RX: C55.3, R95.2
USART2_RX_TELEM1: U10.150 (PD6), U18.1 (A1)
USART2_TX: C55.2, R96.2
USART2_TX_TELEM1: U10.147 (PD5), U18.3 (A2)
USART3_CTS: C56.4, R101.2
USART3_CTS_TELEM2: U10.99 (PD11), U18.8 (A7)
USART3_RTS: C56.5, R102.2
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
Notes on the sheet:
POWER MANAGEMENT
SPI5
FRAM
VER = 0x01
REV = 0x01
CAN BUS
I2C RAIL
VERSION
ADC RAIL
DATA TRANSLATION
PWM I/O
SD CARD
STATUS LEDS
I2C2
DSU7
ADC3/5
I2C3
USART2
USART3
UART4
I2C4
CAN1
CAN2
GPS MODULE
DSM/SBUS RC
PORTS
External Power for Servos
ON-BOARD SENSORS

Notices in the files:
parts and their libraries:
Copyright 2016 Accelerated Designs. All rights reserved.
